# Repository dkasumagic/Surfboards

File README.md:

# Surfboards

This project, albeit confusingly named, is a conceptual demonstrate of creating O(1) matrix multiplication for commercial use, in fields like machine learning for example. 

With matrix multiplication being so fundamental to many modern applications of computer science, and its insistence on being a slow process, it is no wonder that solutions to such an issue are very desirable. One such solution, as simplistic as it may seem, is simply performing more parallel tasks with more cores, and so insert the GPU. But yet still, with the demands of potentially massive matrices, this solution has cost and energy limitations. 

It was these thoughts that pushed our team to attempt to produce O(1) matrix multiplication via bespoke circuit boards that "hardcode" the matrix multiplication algorithm. The idea is to have a program write Verilog code, encoding logic gates that describe this algorithm and then convert this Verilog code into a commercially viable circuit diagram that manufacturers could produce.

# Requirements
- [zig](https://github.com/ziglang/zig)
- [yosys](https://github.com/YosysHQ/yosys)
- [node.js](https://github.com/nodejs/node)
- [npm](https://github.com/npm/cli)

# Installation/Setup
Just run `zig build run` in the project's home directory. Zig compiles the C++ code and runs a webpage on the localhost (see the terminal output for the port). Use from is pretty trivial, although it is left as an exercise for the reader to prove this result.

# Features
The program is accessed throught a locally hosted webpage as so:

The user chooses their desired matrix sizes, with the inner dimensions being locked together to provide valid matrices. The user can also choose the size of their input variables, using the fixed point Q notation, and whether negative values can be used. 

After this, the user presses the generate button and should receive the applicable circuit diagram.

To reduce the monumental space of the chip and to reduce input wires coming into the surfboard, we researched, developed, and implemented a "first-of-its-kind" (that we know of) "proprietary" "symbolic" "vectorised" SVD (Singular Value Decomposition, not to be confused with...) algorithm that can reduce the amount of inputs into the chip by 90%!* 

# Examples/Demos
TODO: insert demo images here please.

# License
This is an open source project under the MIT license - see the LICENSE file if you're struggling to get to sleep.

# Limitations
This is a flawless and fully complete program ready to enable the AI takeover.

# Acknowledgements
Stimulants, sponsors, and sleeplessness.

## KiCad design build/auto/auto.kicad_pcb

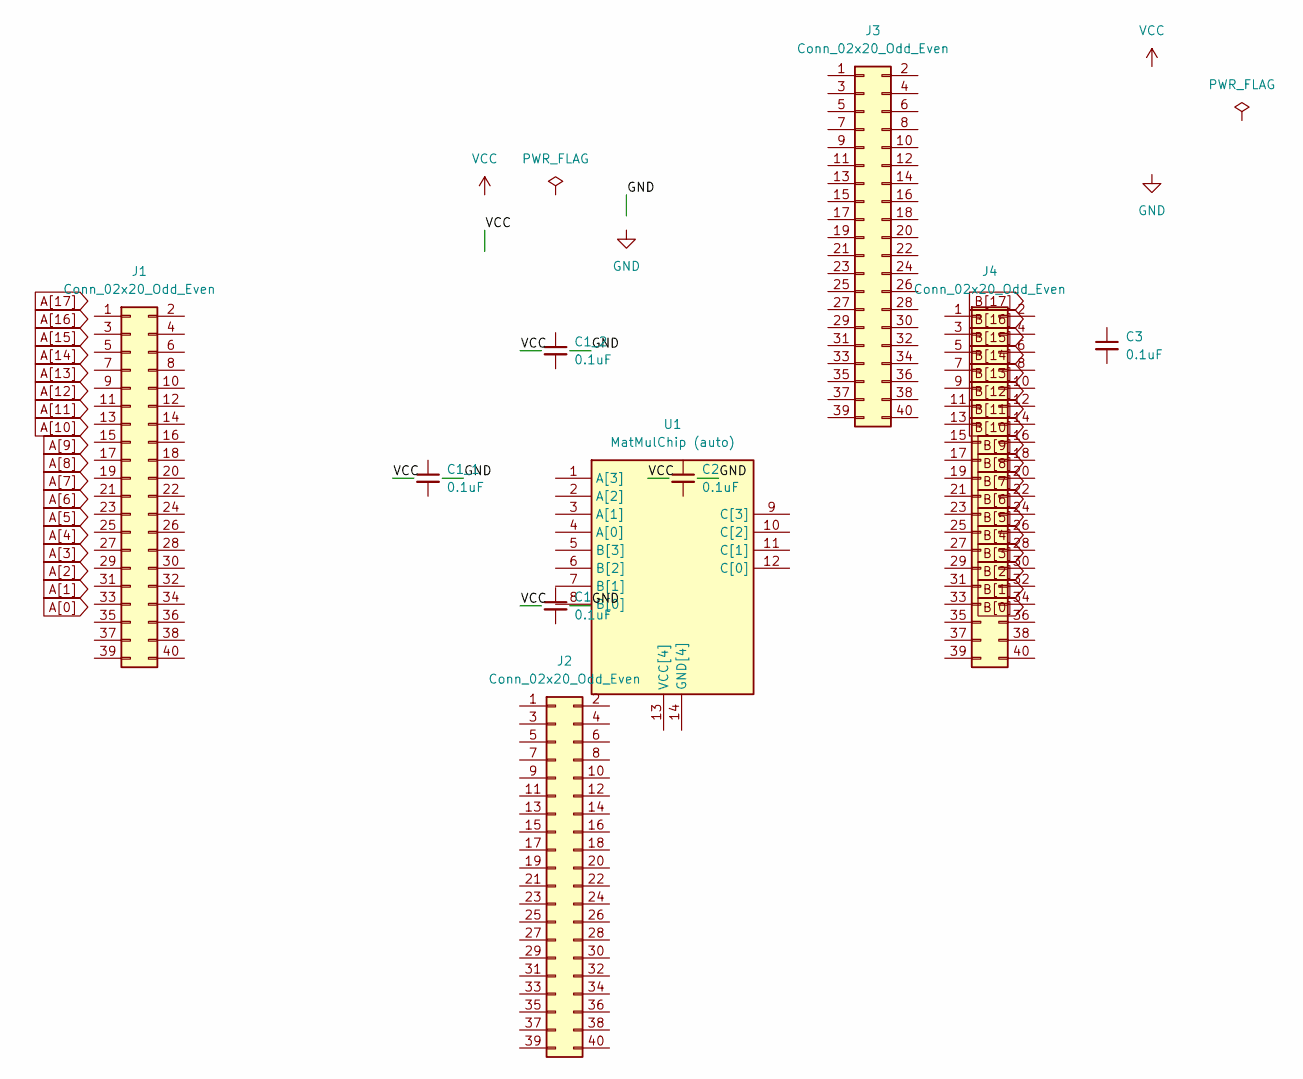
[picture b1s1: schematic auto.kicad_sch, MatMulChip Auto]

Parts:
C1, C1_1, C1_2, C2, C3: 0.1uF; C_0603_1608Metric
J1, J2, J3, J4: Conn_02x20_Odd_Even; PinHeader_2x20_P2.54mm_Vertical
U1: MatMulChip (auto); LQFP-100_14x14mm_P0.5mm

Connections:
unnamed: U1.14 (GND[4]), U1.16 (GND[4]), U1.18 (GND[4]), U1.20 (GND[4])
unnamed: U1.13 (VCC[4]), U1.15 (VCC[4]), U1.17 (VCC[4]), U1.19 (VCC[4])

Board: 2 copper layers, 10 parts (0 on the bottom side), 2 nets, no tracks yet.

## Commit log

2025-08-15 the backend
2025-08-15 files
2025-08-15 first commit!
2025-08-15 Sam getting mad at me for style
2025-08-15 style
2025-08-15 init: zig build system
2025-08-15 some helpful comments and gitignore updates
2025-08-15 comitting because of conflicts
2025-08-15 output directory added
2025-08-15 dev_veri_writer inital commit
2025-08-15 init: zig build system
    init: webui lib
2025-08-15 init: fix entry point and webui lib
2025-08-15 preamble writer
2025-08-15 add: gitmodules
2025-08-15 update: webui server test run
2025-08-15 verilog_writer done! Goodnight :)
2025-08-15 reverting some things for easier merge
2025-08-15 Functional but not tested matrix handler
2025-08-15 Final matrixhandler file. It works! I tested it
2025-08-15 starting on the generator
2025-08-15 gitignore
2025-08-15 progress on generator
2025-08-15 working generator!
2025-08-15 feat: frontend implementation
2025-08-16 aesthetic changes to verilog_writer.cpp
2025-08-16 fix: js file name for default routing. sync a column with b row input box
2025-08-16 feat: write to file from web ui
2025-08-16 renamed this
2025-08-16 renamed visualiser.cpp
2025-08-16 Added output matrix to app function
2025-08-16 feat: generating animation
2025-08-16 feat: dark mode and optional fix floating format
2025-08-16 starting on the symbolic svd algo
2025-08-16 Refactor: verilog_writer.cpp
2025-08-16 Refactor verilog_writer
2025-08-16 Updated app
2025-08-16 a blank slate is needed
2025-08-16 oops
2025-08-16 blank slate
2025-08-16 cleaned up some frontend/backend integration
2025-08-16 minimal changes, just commiting
2025-08-16 blank slate is finished
2025-08-16 manual workflow is functional! todo: automate it
2025-08-16 cleaned some things up
2025-08-16 synthesis_engine is work in progress
2025-08-16 README started and svd_verilog_writer.cpp created
2025-08-16 synthesis engine complete!
2025-08-16 Updated requirements in README
2025-08-16 compartmentalised app.*, added a proper main entry point
2025-08-16 i before e except after c
2025-08-16 FILE ADD svd_verilog_writer.cpp
2025-08-16 accidently deleted app.cpp and pushed to main. Oops!
2025-08-16 enable seemless useage of netlistsvg for all users
2025-08-16 FINISHED svd_verilog_writer.cpp
2025-08-16 Slight adjustments tto svd_verilog_writer
2025-08-17 design.json to 3d model pipeline work in progress
2025-08-17 SVD Engine files uploaded and functional
2025-08-17 feat: signed check button. svd check button. view generated circuit diagram
2025-08-17 bug: populate public folderwith default svg
2025-08-17 feat: singular values input box
2025-08-17 manual design.json -> 3d model workflow complete
2025-08-17 SVD Complete
2025-08-17 feat: 3d view
2025-08-17 README done
2025-08-17 fixed README.md
